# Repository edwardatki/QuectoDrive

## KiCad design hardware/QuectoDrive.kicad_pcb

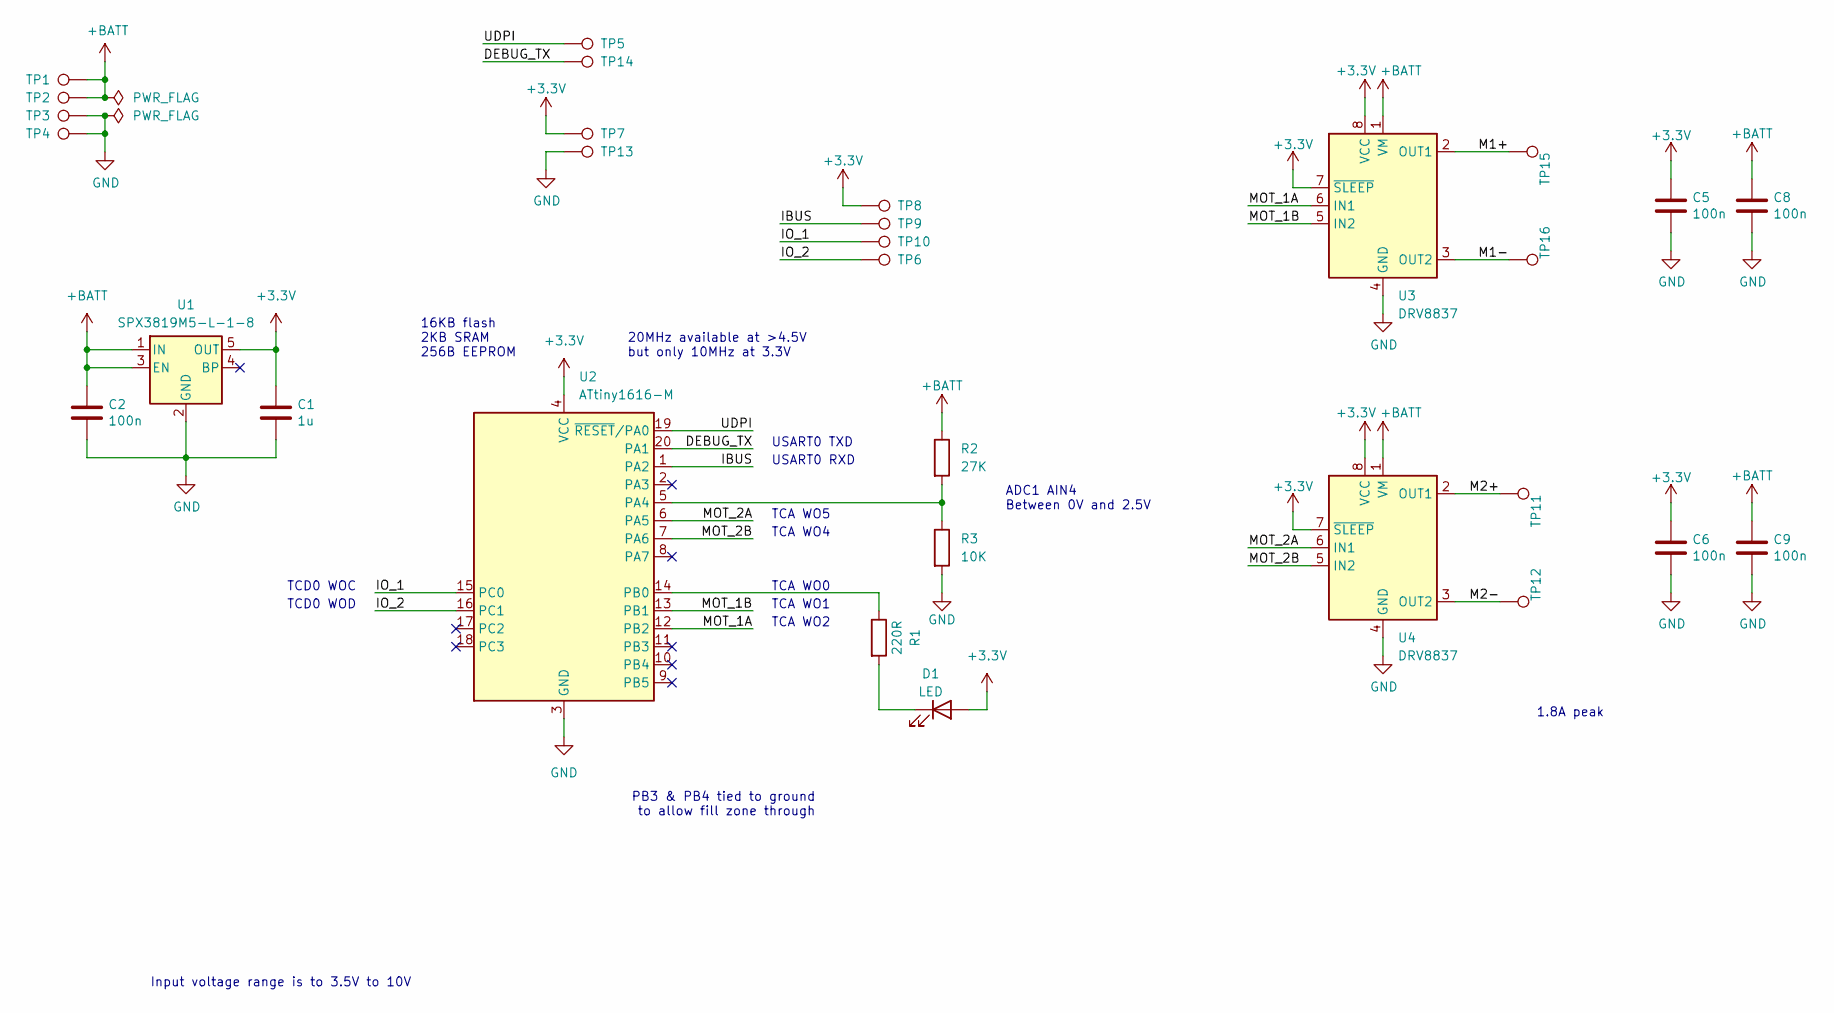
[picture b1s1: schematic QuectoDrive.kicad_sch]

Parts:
C1: 1u; C_0402_1005Metric
C2, C5, C6, C8, C9: 100n; C_0402_1005Metric
D1: LED; LED_0603_1608Metric
R1: 220R; R_0402_1005Metric
R2: 27K; R_0402_1005Metric
R3: 10K; R_0402_1005Metric
TP1, TP2, TP3, TP4: POWER; TestPoint_Pad_2.0x2.0mm
TP5, TP7, TP13, TP14: PROG; TestPoint_Pad_D1.5mm
TP6, TP8, TP9, TP10: IO; TestPoint_Pad_1.5x1.5mm
TP11, TP12, TP15, TP16: MOTOR; TestPoint_Pad_2.0x2.0mm
U1: SPX3819M5-L-1-8; SOT-23-5
U2: ATtiny1616-M; VQFN-20-1EP_3x3mm_P0.4mm_EP1.7x1.7mm
U3, U4: DRV8837; WSON-8-1EP_2x2mm_P0.5mm_EP0.9x1.6mm

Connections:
+3.3V: C1.1, C5.1, C6.1, D1.2 (A), TP7.1, TP8.1, U1.5 (OUT), U2.4 (VCC), U3.7 (~SLEEP), U3.8 (VCC), U4.7 (~SLEEP), U4.8 (VCC)
+BATT: C2.1, C8.1, C9.1, R2.1, TP1.1, TP2.1, U1.1 (IN), U1.3 (EN), U3.1 (VM), U4.1 (VM)
/DEBUG_TX: TP14.1, U2.20 (PA1)
/IBUS: TP9.1, U2.1 (PA2)
/IO_1: TP10.1, U2.15 (PC0)
/IO_2: TP6.1, U2.16 (PC1)
/M1+: TP15.1, U3.2 (OUT1)
/M1-: TP16.1, U3.3 (OUT2)
/M2+: TP11.1, U4.2 (OUT1)
/M2-: TP12.1, U4.3 (OUT2)
/MOT_1A: U2.12 (PB2), U3.6 (IN1)
/MOT_1B: U2.13 (PB1), U3.5 (IN2)
/MOT_2A: U2.6 (PA5), U4.6 (IN1)
/MOT_2B: U2.7 (PA6), U4.5 (IN2)
/UDPI: TP5.1, U2.19 (~RESET/PA0)
GND: C1.2, C2.2, C5.2, C6.2, C8.2, C9.2, R3.2, TP3.1, TP4.1, TP13.1, U1.2 (GND), U2.3 (GND), U2.21 (GND), U3.4 (GND), U3.9 (GND), U4.4 (GND), U4.9 (GND)
unnamed: D1.1 (K), R1.2
unnamed: R2.2, R3.1, U2.5 (PA4)
unnamed: R1.1, U2.14 (PB0)

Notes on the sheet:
20MHz available at >4.5V but only 10MHz at 3.3V
1.8A peak
TCA WO5
Input voltage range is to 3.5V to 10V
ADC1 AIN4 Between 0V and 2.5V
TCD0 WOC
PB3 & PB4 tied to ground to allow fill zone through
16KB flash 2KB SRAM 256B EEPROM
USART0 RXD
TCA WO2
TCA WO4
TCD0 WOD
TCA WO0
USART0 TXD
TCA WO1

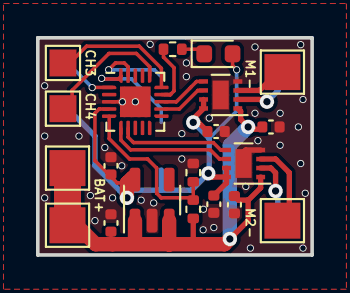
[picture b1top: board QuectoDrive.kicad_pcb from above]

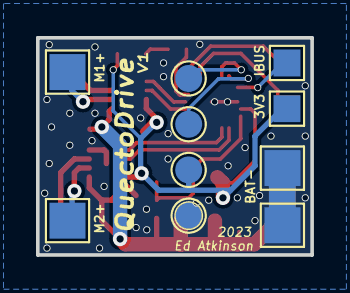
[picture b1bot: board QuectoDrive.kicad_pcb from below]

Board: 2 copper layers, 15.2 x 12.1 mm, 30 parts (10 on the bottom side), 19 nets.

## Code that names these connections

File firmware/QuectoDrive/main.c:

/*
* GccApplication1.c
*
* Created: 26/10/2022 00:33:08
* Author : Edward
*/

#include <avr/io.h>
#include <avr/interrupt.h>

// pymcuprog write -f QuectoDrive.hex  --erase --verify -d attiny1616 -t uart -u com8

#define F_CPU 3300000
#define USART0_BAUD_RATE(BAUD_RATE) ((float)(F_CPU * 64 / (16 * (float)BAUD_RATE)) + 0.5)

#define PER_CELL_CUTOFF 3.0

#define PROTOCOL_LENGTH 0x20
#define PROTOCOL_OVERHEAD 3             // packet is <len><cmd><data....><chkl><chkh>, overhead=cmd+chk bytes
#define PROTOCOL_TIMEGAP 3              // Packets are received every ~7ms so use ~half that for the gap
#define PROTOCOL_CHANNELS 14
#define PROTOCOL_COMMAND_CHANNELS 0x40

float startup_voltage;
float cutoff_voltage;

uint16_t channels [PROTOCOL_CHANNELS] = {1500};
uint32_t last_packet_ms;

volatile uint32_t millis = 0;

ISR(TCB0_INT_vect) {
	TCB0.INTFLAGS = TCB_CAPT_bm;
	millis += 1;
}

// TODO: Implement low voltage cutoff with continuous conversions
ISR(ADC0_WCOMP_vect) {
	
}

// TODO: Fix clock setting, or maybe 3.3MHz is enough
void set_clk(void) {
	//CLKCTRL.MCLKCTRLA = CLKCTRL_CLKSEL_OSC20M_gc;	// Select 20MHz internal oscillator
	//CLKCTRL.MCLKCTRLB = CLKCTRL_PEN_bm			// Enable prescaler
	//				| CLKCTRL_PDIV_2X_gc;			// Set /2 prescaler for 10MHz
}

// Set up an interrupt to fire at 1Khz aka 1ms
void init_systick(void) {
	TCB0.CCMP = 3300;								// Set timer period
	TCB0.CTRLA = TCB_CLKSEL_CLKDIV1_gc				// Select 3.3MHz
			   | TCB_ENABLE_bm						// Enable timer
			   | TCB_RUNSTDBY_bm;					// Start running
	TCB0.CTRLB = TCB_CNTMODE_INT_gc;				// Set mode
	TCB0.INTCTRL = TCB_CAPT_bm;						// Enable interrupt
}

void init_motors(void) {
	TCA0.SINGLE.CTRLD = TCA_SINGLE_SPLITM_bm;		// Enable split mode
	TCA0.SPLIT.HPER = 250;							// Set high timer period of 255
	TCA0.SPLIT.LPER = 250;							// Set low timer period of 255
	TCA0.SPLIT.HCNT = 0;							// Reset high timer initial count
	TCA0.SPLIT.LCNT = 0;							// Reset low timer initial count
	TCA0.SPLIT.CTRLB = TCA_SPLIT_LCMP0EN_bm			// Enable low timer output 0
					 | TCA_SPLIT_LCMP1EN_bm			// Enable low timer output 1
					 | TCA_SPLIT_LCMP2EN_bm			// Enable low timer output 2
					//| TCA_SPLIT_HCMP0EN_bm		// Enable high timer output 0
					//| TCA_SPLIT_HCMP1EN_bm		// Enable high timer output 1
					 | TCA_SPLIT_HCMP2EN_bm;		// Enable high timer output 2
	TCA0.SPLIT.CTRLA = TCA_SPLIT_CLKSEL_DIV1_gc		// Set /1 clock prescaler for 3.3MHz
					 | TCA_SPLIT_ENABLE_bm;			// Start timer
	
	// 3.3MHz/250, final period is 13.2KHz I think
	// DRV8837 says 250KHz max, frequency doesn't seems effect performance
	// Higher frequency has less whine so we've gone highest possible
	
	TCA0.SPLIT.LCMP0 = 0;							// Set initial value to 0
	TCA0.SPLIT.LCMP1 = 0;							// Set initial value to 0
	TCA0.SPLIT.LCMP2 = 0;							// Set initial value to 0
	//TCA0.SPLIT.HCMP0 = 0;							// Set initial value to 0
	//TCA0.SPLIT.HCMP1 = 0;							// Set initial value to 0
	TCA0.SPLIT.HCMP2 = 0;							// Set initial value to 0
	
	//PORTMUX.CTRLC |= PORTMUX_TCA02_bm;			// Map WO2 to alternate PB5
	PORTB.DIRSET = PIN0_bm;							// Set PB0 as output
	PORTB.DIRSET = PIN1_bm;							// Set PB1 as output
	PORTB.DIRSET = PIN2_bm;							// Set PB2 as output
	PORTB.DIRSET = PIN5_bm;							// Set PB5 as output
	PORTA.DIRSET = PIN5_bm;							// Set PA5 as output
}

void init_weapons(void) {
	TCD0.CTRLB = TCD_WGMODE_ONERAMP_gc;				// Single ramp mode
	
	CPU_CCP = CCP_IOREG_gc;							// Enable write protected register
	TCD0.FAULTCTRL = TCD_CMPCEN_bm;					// Enable WOC
	
	TCD0.CMPACLR = 2062;							// Period of 2062 for 20ms period
	TCD0.CMPBCLR = 2062;
	TCD0.CMPASET = 2062-103;							// 103 to 206 for 1.03ms to 2.06ms
	TCD0.CMPBSET = 2062-103;
	
	while(!(TCD0.STATUS & TCD_ENRDY_bm)) {}			// Ensure ENRDY bit is set
	
	TCD0.CTRLA = TCD_CLKSEL_SYSCLK_gc				// Choose 3.3MHz clock
			   | TCD_SYNCPRES_DIV1_gc
			   | TCD_CNTPRES_DIV32_gc				// Choose /32 prescaler for 103.1KHz
			   | TCD_ENABLE_bm;						// Enable timer
	
	PORTC.DIRSET = PIN0_bm;							// Set PC0 as output
}

// THIS IS ALL BROKEN I THINK
void init_adc_and_cutoff(void) {
	// Configured to get 94 readings per second
	ADC0.CTRLB = ADC_SAMPNUM_ACC64_gc;				// Take 64 samples per reading
	ADC0.CTRLC = ADC_REFSEL_VDDREF_gc				// Select VDD as reference
				| ADC_PRESC_DIV128_gc;				// Select /128 prescaler for 78KHz
	ADC0.CTRLA = ADC_RESSEL_10BIT_gc				// Set 10 bit resolution
				| ADC_FREERUN_bm					// Set free-running
				| ADC_ENABLE_bm;					// Enable
	ADC0.MUXPOS = ADC_MUXPOS4_bm;					// Set PA1 as input
	ADC0.COMMAND = ADC_STCONV_bm;					// Start running
	
	// Wait for first conversion to complete
	while (ADC0.INTFLAGS & ADC_RESRDY_bm) continue;
	
	// Figure out cell count and appropriate window threshold
	float conversion_factor = (3.3/(1 << 10))*(10.0/37.0);
	startup_voltage = ADC0.RES * conversion_factor;
	uint8_t cell_count = startup_voltage / PER_CELL_CUTOFF;
	cutoff_voltage = PER_CELL_CUTOFF * cell_count;
	
	// TODO: setup interrupts for conversion complete
}

void init_uart(void) {
	PORTMUX.CTRLB |= PORTMUX_USART0_bm;				// Set USART0 alternate pins
	PORTA.DIRCLR = PIN2_bm;							// Set PA2 as input
	
	USART0.BAUD = (uint16_t)USART0_BAUD_RATE(115200);
	USART0.CTRLB = USART_RXEN_bm;					// Enable receive pin
	
	USART0.CTRLC = USART_CMODE_ASYNCHRONOUS_gc
				| USART_CHSIZE_8BIT_gc
				| USART_PMODE_DISABLED_gc
				| USART_SBMODE_1BIT_gc;
}

// TODO if transmitter turned off and on then controls stutter and lag
void ibus_update(void) {
	enum {GET_LENGTH, GET_DATA, GET_CHKSUML, GET_CHKSUMH, DISCARD};

	static uint32_t last_byte_ms;					// Timestamp of last byte
	static uint8_t state = DISCARD;					// Receive state
	static uint8_t buffer[PROTOCOL_LENGTH];			// Message buffer
	static uint8_t ptr;								// Pointer in buffer
	static uint8_t length;							// Message length
	static uint16_t chksum;							// Calculated checksum
	static uint8_t lchksum;							// Received checksum lower byte
	
	if (USART0.STATUS & USART_RXCIF_bm) {
		// Only consider a new data packet if we have not heard anything for >3ms
		uint32_t now = millis;
		if ((now - last_byte_ms) >= PROTOCOL_TIMEGAP) {
			state = GET_LENGTH;
		}
		last_byte_ms = now;

		uint8_t byte =  USART0.RXDATAL;
		switch (state) {
			case GET_LENGTH:
				if ((byte <= PROTOCOL_LENGTH) & (byte > PROTOCOL_OVERHEAD)) {
					ptr = 0;
					length = byte - PROTOCOL_OVERHEAD;
					chksum = 0xFFFF - byte;
					state = GET_DATA;
				} else {
					state = DISCARD;
				}
				break;
			
			case GET_DATA:
				buffer[ptr++] = byte;
				chksum -= byte;
				if (ptr == length) {
					state = GET_CHKSUML;
				}
				break;
			
			case GET_CHKSUML:
				lchksum = byte;
				state = GET_CHKSUMH;
				break;
			
			case GET_CHKSUMH:
				// Validate checksum
				if (chksum == ((byte << 8) + lchksum)) {
					// Checksum is all fine so execute command
					if (buffer[0] == PROTOCOL_COMMAND_CHANNELS) {
						// Channel data command
						for (uint8_t i = 1; i < PROTOCOL_CHANNELS * 2 + 1; i += 2) {
							channels[i / 2] = buffer[i] | (buffer[i + 1] << 8);
						}
					}
					
					// Update last valid packet timestamp
					last_packet_ms = millis;
				}
				state = DISCARD;
				break;

			default:
				break;
		}
	}
}

void set_led(uint8_t value) {
	TCA0.SPLIT.LCMP0 = value;
}

void set_motor_a(int16_t value) {
	if (value > 250) value = 250;
	if (value < -250) value = -250;
	
	if (value > 0) {
		TCA0.SPLIT.LCMP1 = 250-value;
		TCA0.SPLIT.LCMP2 = 250;
	} else if (value < 0) {
		TCA0.SPLIT.LCMP1 = 250;
		TCA0.SPLIT.LCMP2 = 250+value;
	} else {
		TCA0.SPLIT.LCMP1 = 250;
		TCA0.SPLIT.LCMP2 = 250;
	}
}

void set_motor_b(int16_t value) {
	if (value > 250) value = 250;
	if (value < -250) value = -250;
	
	if (value > 0) {
		PORTB.OUTCLR = 1 << 5;
		TCA0.SPLIT.HCMP2 = 0+value;
	} else if (value < 0) {
		PORTB.OUTSET = 1 << 5;
		TCA0.SPLIT.HCMP2 = 250+value;
	} else {
		PORTB.OUTSET = 1 << 5;
		TCA0.SPLIT.HCMP2 = 250;
	}
}

void set_weapon_a(uint16_t value) {
		// Need to map 1000-2000 to 103-206
		// Only managed 100-200
		TCD0.CMPASET = 2062-(value/10);
		TCD0.CTRLE = TCD_SYNCEOC_bm;
}

int main(void) {
	//set_clk();
	init_motors();
	init_weapons();
	//init_adc_and_cutoff();
	init_uart();
	init_systick();

	sei();

	while (1) {
		// Read data from receiver
		ibus_update();
		
		if (millis-last_packet_ms < 100) {
			set_led(5);
			
			// Update motor speeds
			int16_t fb = ((int16_t)channels[0]-1500)/2;
			int16_t lr = ((int16_t)channels[1]-1500)/2;
			set_motor_a(fb+lr);
			set_motor_b(fb-lr);
			set_weapon_a(channels[2]);
		} else {
			set_led(0);
			
			// Stop motors
			set_motor_a(0);
			set_motor_b(0);
			set_weapon_a(0);
		}
	}
}

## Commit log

2023-01-22 Initial commit
    As ordered on 22/01/2023
2023-02-06 Early working firmware
    PWM pins for motors 1 and 2 conflict, oops
    ibus decoding working
    Motor 1 working
    Motor 2 can be made to work but will lack braking in one direction
2023-03-22 IO pad PWM outputs
2023-03-31 Board Rev 2
